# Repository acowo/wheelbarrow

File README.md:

# wheelbarrow
 A HHKB 40% based on the Arrow40 designed by Snurrebassen.

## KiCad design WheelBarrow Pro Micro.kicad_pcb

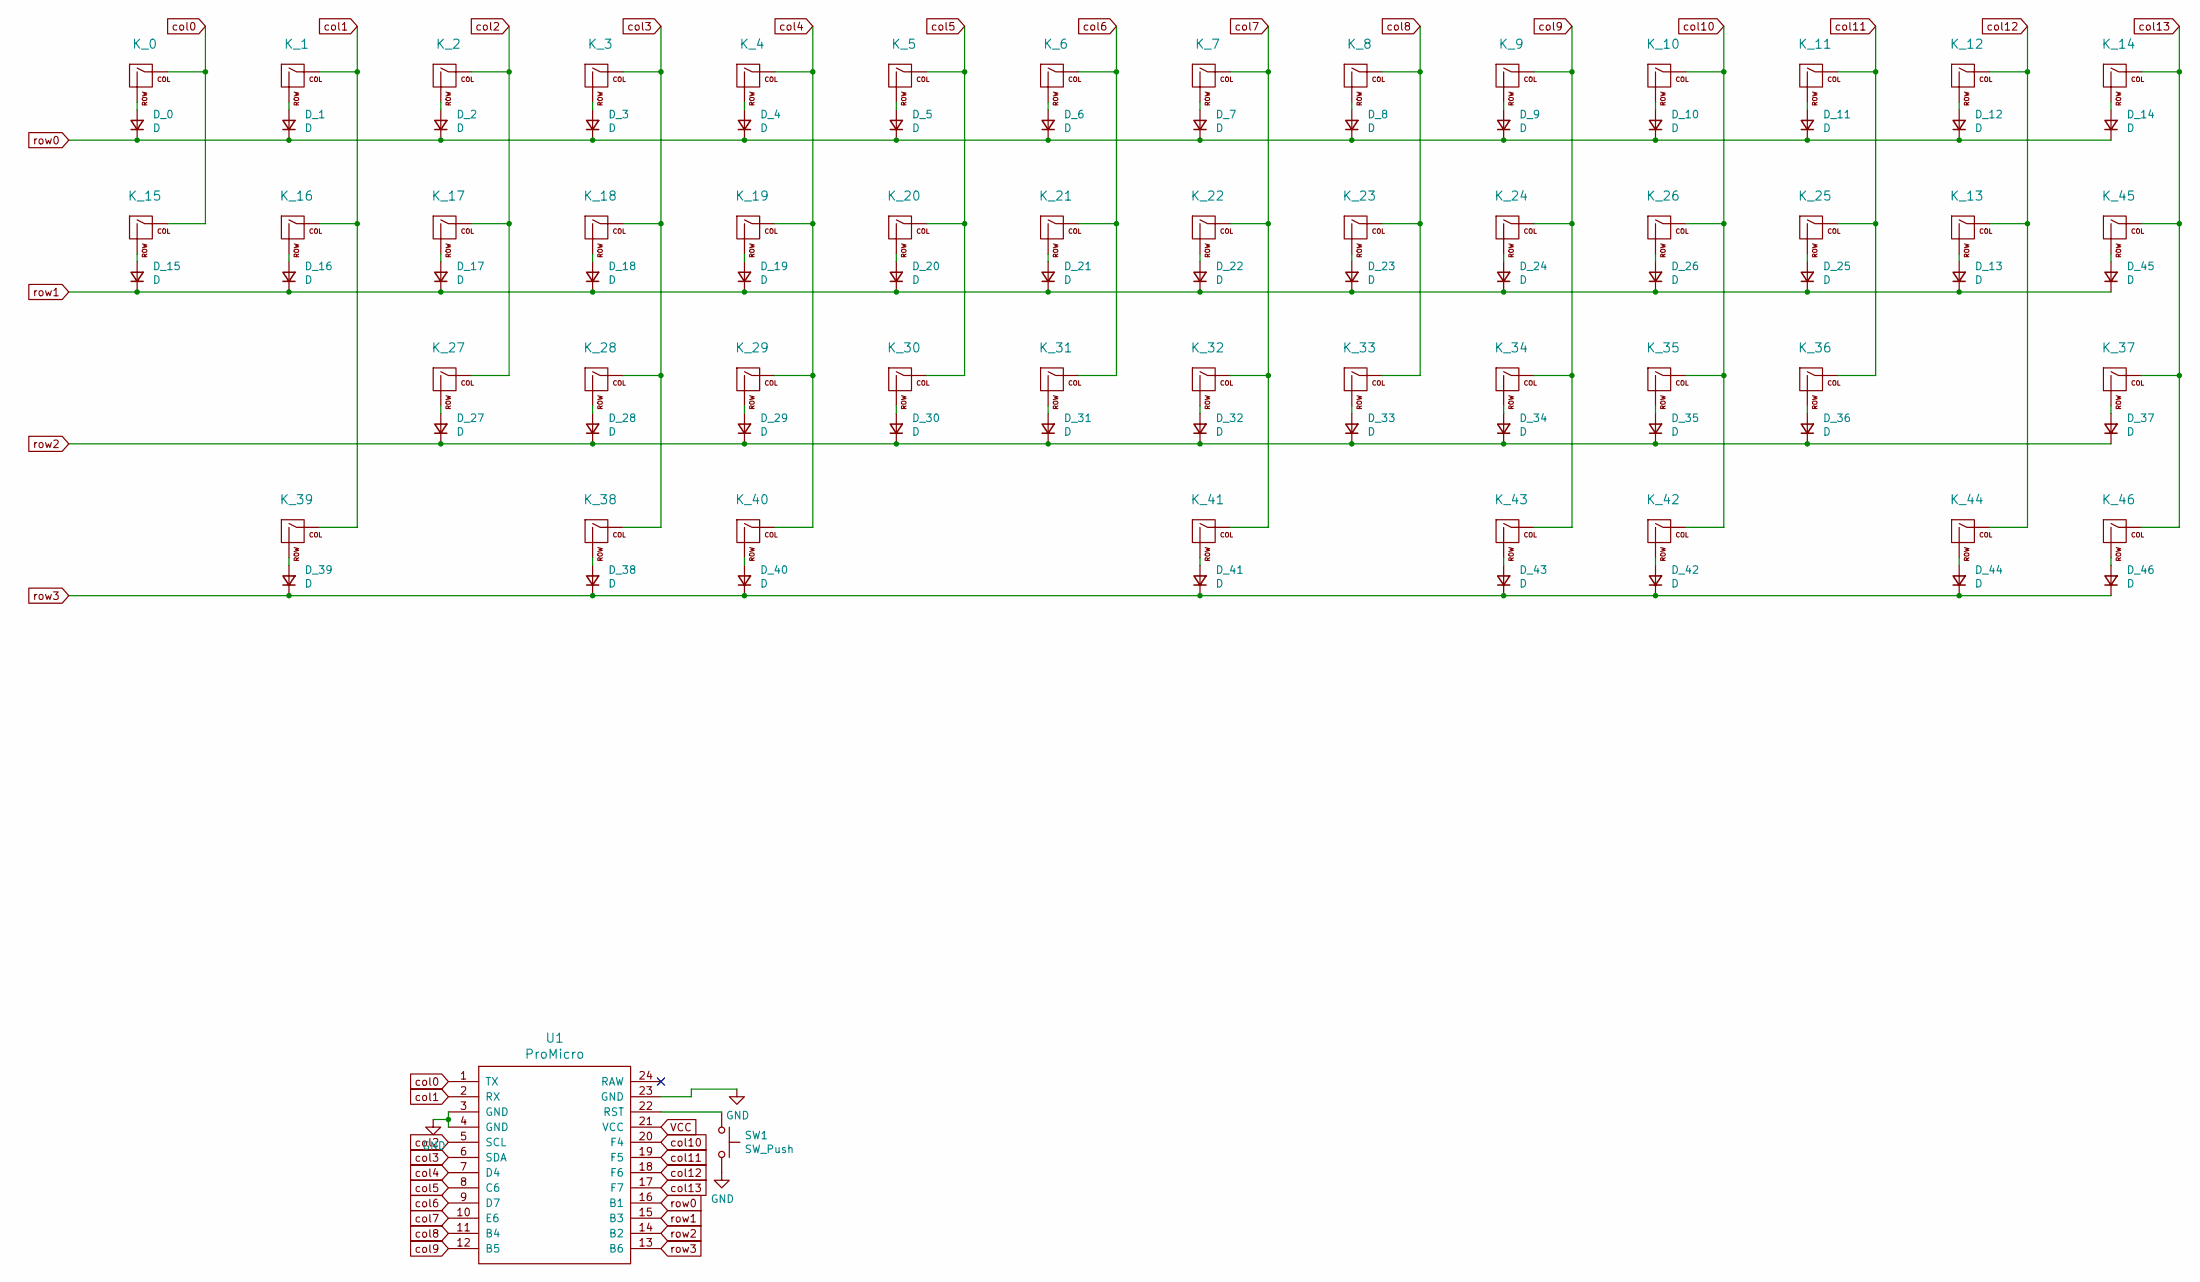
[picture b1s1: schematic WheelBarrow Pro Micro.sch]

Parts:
D_0, D_1, D_2, D_3, D_4, D_5, D_6, D_7, D_8, D_9, D_10, D_11, D_12, D_13, D_14, D_15, D_16, D_17, D_18, D_19, D_20, D_21, D_22, D_23, D_24, D_25, D_26, D_27, D_28, D_29, D_30, D_31, D_32, D_33, D_34, D_35, D_36, D_37, D_38, D_39, D_40, D_41, D_42, D_43, D_44, D_45, D_46: D; D_SOD-123
K_0, K_1, K_2, K_3, K_4, K_5, K_6, K_7, K_8, K_9, K_10, K_11, K_12, K_13, K_14, K_16, K_17, K_18, K_19, K_20, K_21, K_22, K_23, K_24, K_27, K_28, K_29, K_30, K_31, K_32, K_33, K_34, K_35, K_37, K_39, K_42, K_44, K_45, K_46: KEYSW; MX-1U-NoLED
K_15, K_36: KEYSW; MX-1.25U-NoLED
K_25, K_26: KEYSW; MX-1.75U-NoLED
K_38, K_43: KEYSW; MX-1.5U-NoLED
K_40: KEYSW; MX-2.25U-NoLED
K_41: KEYSW; MX-2.75U-NoLED
SW1: SW_Push; SW_SPST_SKQG_WithStem
U1: ProMicro

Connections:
GND: SW1.2, U1.3 (GND), U1.4 (GND), U1.23 (GND)
unnamed: D_0.2 (A), K_0.2 (ROW)
unnamed: D_1.2 (A), K_1.2 (ROW)
unnamed: D_2.2 (A), K_2.2 (ROW)
unnamed: D_3.2 (A), K_3.2 (ROW)
unnamed: D_4.2 (A), K_4.2 (ROW)
unnamed: D_5.2 (A), K_5.2 (ROW)
unnamed: D_6.2 (A), K_6.2 (ROW)
unnamed: D_7.2 (A), K_7.2 (ROW)
unnamed: D_8.2 (A), K_8.2 (ROW)
unnamed: D_9.2 (A), K_9.2 (ROW)
unnamed: D_10.2 (A), K_10.2 (ROW)
unnamed: D_11.2 (A), K_11.2 (ROW)
unnamed: D_12.2 (A), K_12.2 (ROW)
unnamed: D_13.2 (A), K_13.2 (ROW)
unnamed: D_14.2 (A), K_14.2 (ROW)
unnamed: D_15.2 (A), K_15.2 (ROW)
unnamed: D_16.2 (A), K_16.2 (ROW)
unnamed: D_17.2 (A), K_17.2 (ROW)
unnamed: D_18.2 (A), K_18.2 (ROW)
unnamed: D_19.2 (A), K_19.2 (ROW)
unnamed: D_20.2 (A), K_20.2 (ROW)
unnamed: D_21.2 (A), K_21.2 (ROW)
unnamed: D_22.2 (A), K_22.2 (ROW)
unnamed: D_23.2 (A), K_23.2 (ROW)
unnamed: D_24.2 (A), K_24.2 (ROW)
unnamed: D_25.2 (A), K_25.2 (ROW)
unnamed: D_26.2 (A), K_26.2 (ROW)
unnamed: D_27.2 (A), K_27.2 (ROW)
unnamed: D_28.2 (A), K_28.2 (ROW)
unnamed: D_29.2 (A), K_29.2 (ROW)
unnamed: D_30.2 (A), K_30.2 (ROW)
unnamed: D_31.2 (A), K_31.2 (ROW)
unnamed: D_32.2 (A), K_32.2 (ROW)
unnamed: D_33.2 (A), K_33.2 (ROW)
unnamed: D_34.2 (A), K_34.2 (ROW)
unnamed: D_35.2 (A), K_35.2 (ROW)
unnamed: D_36.2 (A), K_36.2 (ROW)
unnamed: D_37.2 (A), K_37.2 (ROW)
unnamed: D_38.2 (A), K_38.2 (ROW)
unnamed: D_39.2 (A), K_39.2 (ROW)
unnamed: D_40.2 (A), K_40.2 (ROW)
unnamed: D_41.2 (A), K_41.2 (ROW)
unnamed: D_42.2 (A), K_42.2 (ROW)
unnamed: D_43.2 (A), K_43.2 (ROW)
unnamed: D_44.2 (A), K_44.2 (ROW)
unnamed: D_45.2 (A), K_45.2 (ROW)
unnamed: D_46.2 (A), K_46.2 (ROW)
unnamed: SW1.1, U1.22 (RST)
VCC: U1.21 (VCC)
col0: K_0.1 (COL), K_15.1 (COL), U1.1 (TX)
col1: K_1.1 (COL), K_16.1 (COL), K_39.1 (COL), U1.2 (RX)
col2: K_2.1 (COL), K_17.1 (COL), K_27.1 (COL), U1.5 (SCL)
col3: K_3.1 (COL), K_18.1 (COL), K_28.1 (COL), K_38.1 (COL), U1.6 (SDA)
col4: K_4.1 (COL), K_19.1 (COL), K_29.1 (COL), K_40.1 (COL), U1.7 (D4)
col5: K_5.1 (COL), K_20.1 (COL), K_30.1 (COL), U1.8 (C6)
col6: K_6.1 (COL), K_21.1 (COL), K_31.1 (COL), U1.9 (D7)
col7: K_7.1 (COL), K_22.1 (COL), K_32.1 (COL), K_41.1 (COL), U1.10 (E6)
col8: K_8.1 (COL), K_23.1 (COL), K_33.1 (COL), U1.11 (B4)
col9: K_9.1 (COL), K_24.1 (COL), K_34.1 (COL), K_43.1 (COL), U1.12 (B5)
col10: K_10.1 (COL), K_26.1 (COL), K_35.1 (COL), K_42.1 (COL), U1.20 (F4)
col11: K_11.1 (COL), K_25.1 (COL), K_36.1 (COL), U1.19 (F5)
col12: K_12.1 (COL), K_13.1 (COL), K_44.1 (COL), U1.18 (F6)
col13: K_14.1 (COL), K_37.1 (COL), K_45.1 (COL), K_46.1 (COL), U1.17 (F7)
row0: D_0.1 (K), D_1.1 (K), D_2.1 (K), D_3.1 (K), D_4.1 (K), D_5.1 (K), D_6.1 (K), D_7.1 (K), D_8.1 (K), D_9.1 (K), D_10.1 (K), D_11.1 (K), D_12.1 (K), D_14.1 (K), U1.16 (B1)
row1: D_13.1 (K), D_15.1 (K), D_16.1 (K), D_17.1 (K), D_18.1 (K), D_19.1 (K), D_20.1 (K), D_21.1 (K), D_22.1 (K), D_23.1 (K), D_24.1 (K), D_25.1 (K), D_26.1 (K), D_45.1 (K), U1.15 (B3)
row2: D_27.1 (K), D_28.1 (K), D_29.1 (K), D_30.1 (K), D_31.1 (K), D_32.1 (K), D_33.1 (K), D_34.1 (K), D_35.1 (K), D_36.1 (K), D_37.1 (K), U1.14 (B2)
row3: D_38.1 (K), D_39.1 (K), D_40.1 (K), D_41.1 (K), D_42.1 (K), D_43.1 (K), D_44.1 (K), D_46.1 (K), U1.13 (B6)

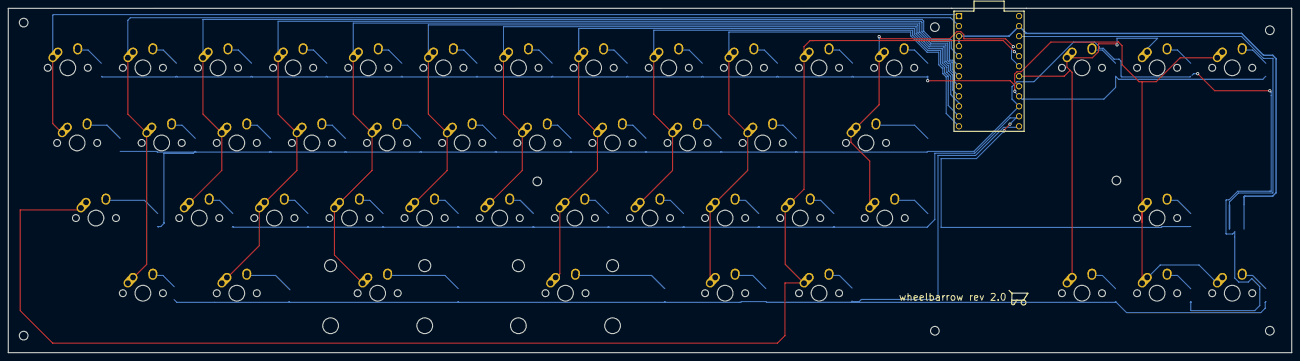
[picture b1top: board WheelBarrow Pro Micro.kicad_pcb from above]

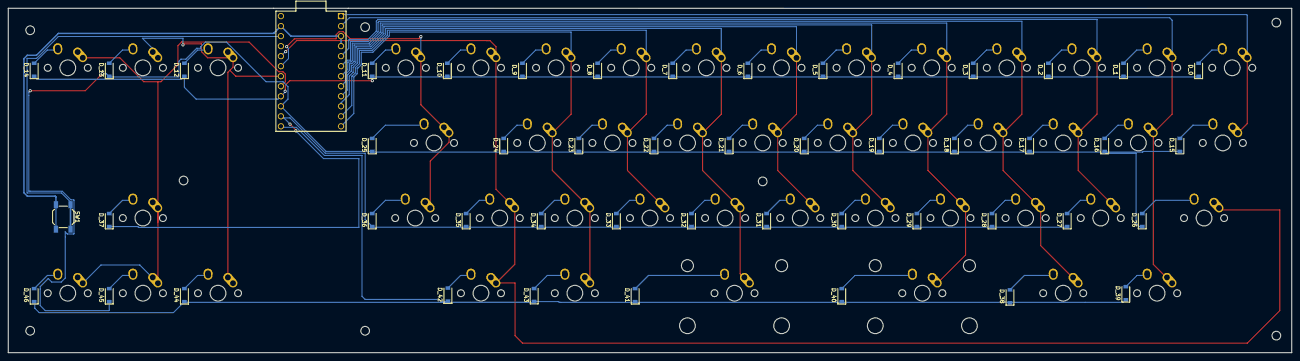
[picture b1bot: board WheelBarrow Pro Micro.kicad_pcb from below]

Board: 2 copper layers, 325.4 x 87.3 mm, 96 parts (48 on the bottom side), 67 nets.

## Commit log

2021-08-06 Adding keyboard files
